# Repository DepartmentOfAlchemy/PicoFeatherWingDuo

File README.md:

# ProtoPropDuo
Breakout board allowing a Raspberry Pi Pico to interface with up to two FeatherWing boards.

RP2040 Peripheral Usage for Feather Wings

SPI:
  * SCK: SPI1 SCK
  * MOSI: SPI1 TX
  * MISO: SPI1 RX

I2C:
  * SDA: I2C1 SDA
  * SCL: I2C1 SCL

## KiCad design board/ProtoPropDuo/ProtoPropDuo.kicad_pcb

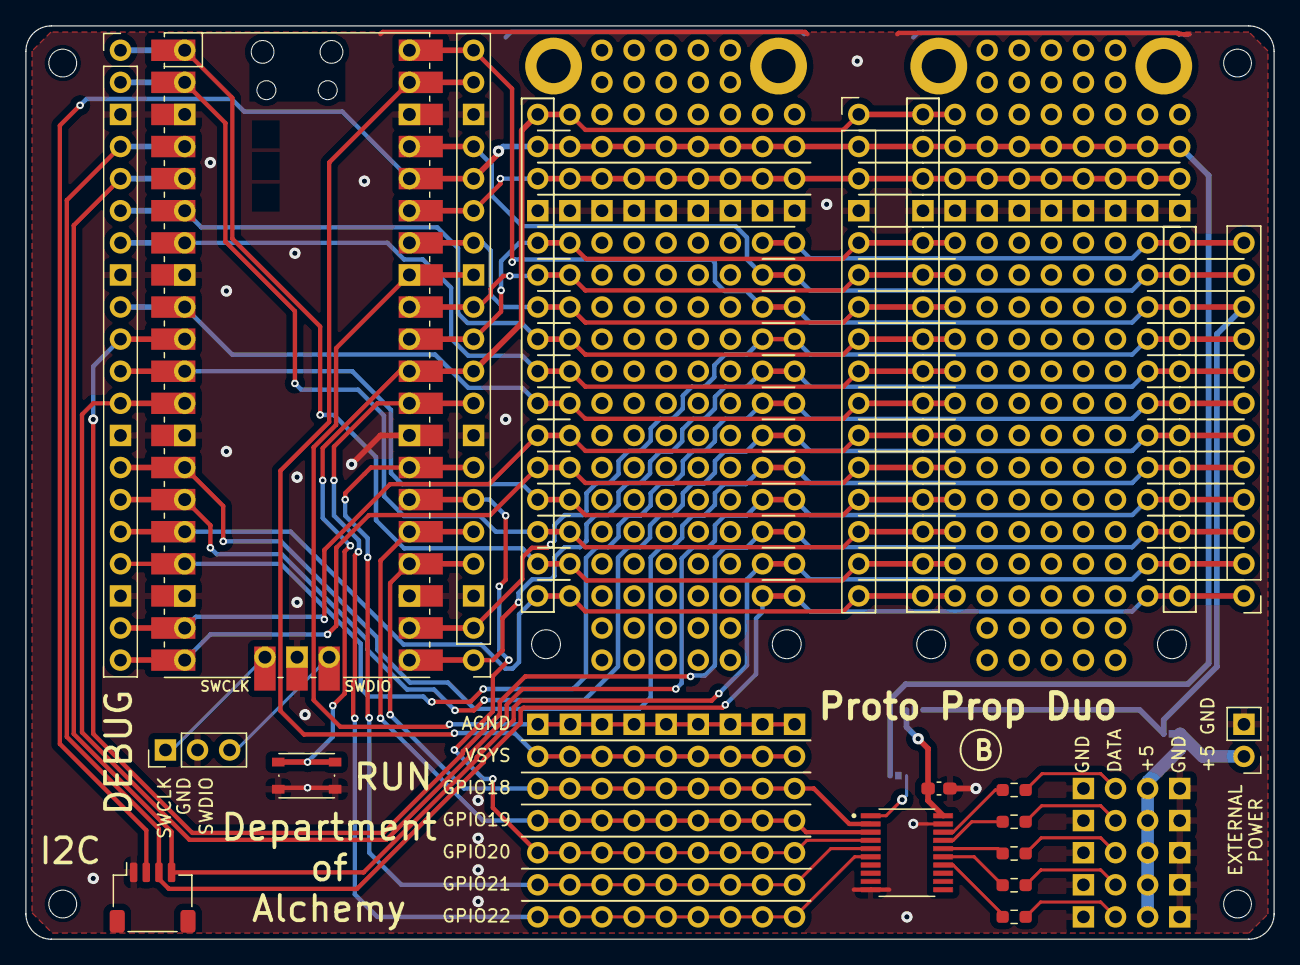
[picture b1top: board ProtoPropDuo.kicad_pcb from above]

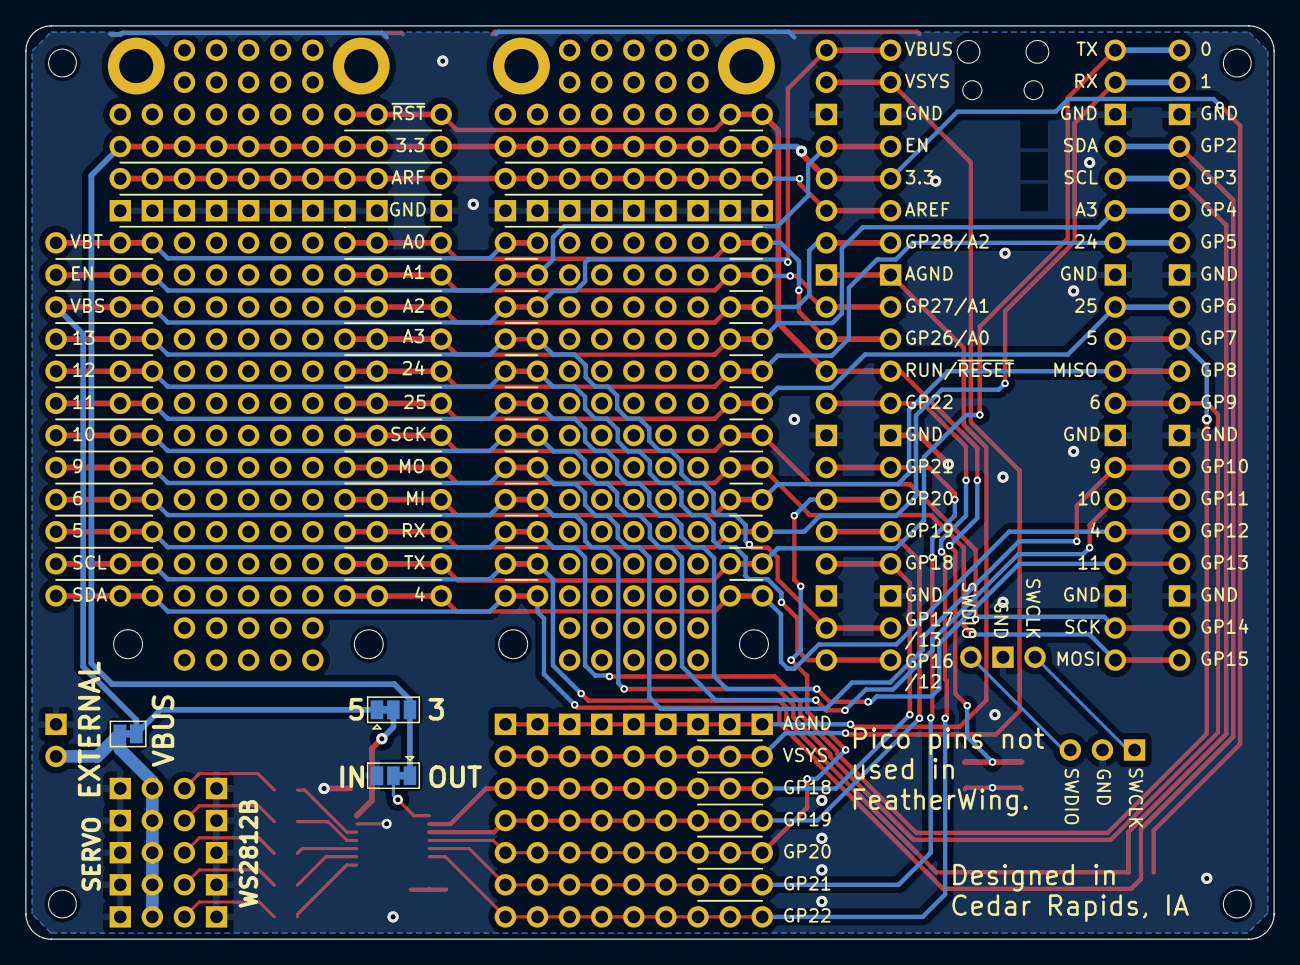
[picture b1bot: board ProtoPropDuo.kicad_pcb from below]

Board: 2 copper layers, 98.8 x 72.3 mm, 183 parts (3 on the bottom side), 50 nets.

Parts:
A1, A2: Adafruit_Feather_Generic; Feather Pins
C1: 0.1uF; C_0603_1608Metric_Pad1.08x0.95mm_HandSolder
H1, H2, H3, H4: MountingHole; MountingHole_2.2mm_M2_ISO14580
J1: Conn_01x04; JST_SH_SM04B-SRSS-TB_1x04-1MP_P1.00mm_Horizontal
J2: Conn_01x07; PinHeader_1x07_P2.54mm_Vertical
J3, J4: Conn_01x20; PinHeader_1x20_P2.54mm_Vertical
J5: Conn_01x16; PinHeader_1x16_P2.54mm_Vertical
J6: Conn_01x12; PinHeader_1x12_P2.54mm_Vertical
J7, J8, J9, J10, J11, J12, J13, J14, J15, J16, J17, J18, J19, J20, J21, J22, J23, J24, J25, J26, J27, J28, J29, J30, J31, J32, J33, J34, J35, J36, J37, J38, J39, J40, J41, J42, J43, J44, J45, J46, J47, J48, J49, J50, J51, J52, J53, J54, J55, J56, J57, J58, J59, J60, J61, J62, J63, J64, J65, J66, J67, J68, J69, J70, J71, J72, J73, J74, J75, J76, J77, J78, J79, J80, J81, J82, J83, J84, J85, J86, J87, J88, J89, J90, J91, J92, J93, J94, J95, J96, J97, J98, J99, J100, J101, J102, J103, J104, J105, J107, J108, J109, J110, J110#2, J110#3, J110#4, J110#5, J110#6, J110#7, J111, J113, J113#2, J113#3, J113#4, J113#5, J113#6, J114, J114#2, J114#3, J114#4, J114#5, J114#6, J114#7, J115, J115#2, J115#3, J115#4, J115#5, J115#6, J115#7, J116, J116#2, J116#3, J116#4, J116#5, J116#6, J116#7, J117, J118, J118#2, J118#3, J118#4, J118#5, J118#6, J118#7, J119, J120, J120#2, J120#3, J120#4, J120#5, J120#6, J120#7: Conn_01x01; Grid Hole
J106, J112, J124: Conn_01x05; PinHeader_1x05_P2.54mm_Vertical
J121: Conn_01x03; PinHeader_1x03_P2.54mm_Vertical
J122: Conn_01x02; PinHeader_1x02_P2.54mm_Vertical
J123: Conn_01x05_Extra_Output; PinHeader_1x05_P2.54mm_Vertical
JP1: SolderJumper_2_Bridged; SolderJumper-2_P1.3mm_Bridged_Pad1.0x1.5mm
JP2, JP3: SolderJumper_3_Bridged12; SolderJumper-3_P1.3mm_Bridged12_Pad1.0x1.5mm
R1, R2, R3, R4, R5: 300; R_0603_1608Metric_Pad0.98x0.95mm_HandSolder
SW2: SW_Push; SW_Push_1P1T_NO_RKB2SJK250SMTR LFS
U1: Pico; RPi_Pico_SMD_TH
U2: SOP65P640X120-20N

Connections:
+3.3V: A1.2 (3V3), A2.2 (3V3), J1.2, J4.16, J5.2, J9.1, J37.1, J92.1, J93.1, J94.1, J95.1, J96.1, J97.1, J98.1, J99.1, J100.1, J101.1, J102.1, J103.1, J104.1, J105.1, JP2.3 (B), JP3.1 (A), U1.36 (3V3)
+5V: J106.1, J106.2, J106.3, J106.4, J106.5, J122.1, JP1.2 (B)
/A0: A1.5 (A0), A2.5 (A0), J4.11, J5.5, J12.1, J40.1, U1.31 (GPIO26_ADC0)
/A1: A1.6 (A1), A2.6 (A1), J4.12, J5.6, J13.1, J41.1, U1.32 (GPIO27_ADC1)
/A2: A1.7 (A2), A2.7 (A2), J4.14, J5.7, J14.1, J42.1, U1.34 (GPIO28_ADC2)
/A3: A1.8 (A3), A2.8 (A3), J3.6, J5.8, J15.1, J43.1, U1.6 (GPIO4)
/AGND: J2.1, J4.13, J119.1, J120.1, J120#2.1, J120#3.1, J120#4.1, J120#5.1, J120#6.1, J120#7.1, U1.33 (AGND)
/AREF: A1.3 (AREF), A2.3 (AREF), J4.15, J5.3, J10.1, J38.1, J78.1, J79.1, J80.1, J81.1, J82.1, J83.1, J84.1, J85.1, J86.1, J87.1, J88.1, J89.1, J90.1, J91.1, U1.35 (ADC_VREF)
/D4: A1.16 (SPARE), A2.16 (SPARE), J3.16, J5.16, J23.1, J51.1, U1.16 (GPIO12)
/D5: A1.19 (D5), A2.19 (D5), J3.10, J6.3, J33.1, J61.1, U1.10 (GPIO7)
/D6: A1.20 (D6), A2.20 (D6), J3.12, J6.4, J32.1, J60.1, U1.12 (GPIO9)
/D9: A1.21 (D9), A2.21 (D9), J3.14, J6.5, J31.1, J59.1, U1.14 (GPIO10)
/D10: A1.22 (D10), A2.22 (D10), J3.15, J6.6, J30.1, J58.1, U1.15 (GPIO11)
/D11: A1.23 (D11), A2.23 (D11), J3.17, J6.7, J29.1, J57.1, U1.17 (GPIO13)
/D12: A1.24 (D12), A2.24 (D12), J4.1, J6.8, J28.1, J56.1, U1.21 (GPIO16)
/D13: A1.25 (D13), A2.25 (D13), J4.2, J6.9, J27.1, J55.1, U1.22 (GPIO17)
/D24: A1.9 (A4), A2.9 (A4), J3.7, J5.9, J16.1, J44.1, U1.7 (GPIO5)
/D25: A1.10 (A5), A2.10 (A5), J3.9, J5.10, J17.1, J45.1, U1.9 (GPIO6)
/EN: A1.27 (EN), A2.27 (EN), J4.17, J6.11, J25.1, J53.1, U1.37 (3V3_EN)
/GPIO18: J2.3, J4.4, J110.1, J110#2.1, J110#3.1, J110#4.1, J110#5.1, J110#6.1, J110#7.1, J117.1, U1.24 (GPIO18), U2.2 (A0)
/GPIO19: J2.4, J4.5, J109.1, J116.1, J116#2.1, J116#3.1, J116#4.1, J116#5.1, J116#6.1, J116#7.1, U1.25 (GPIO19), U2.3 (A1)
/GPIO20: J2.5, J4.6, J108.1, J115.1, J115#2.1, J115#3.1, J115#4.1, J115#5.1, J115#6.1, J115#7.1, U1.26 (GPIO20), U2.4 (A2)
/GPIO21: J2.6, J4.7, J107.1, J114.1, J114#2.1, J114#3.1, J114#4.1, J114#5.1, J114#6.1, J114#7.1, U1.27 (GPIO21), U2.5 (A3)
/GPIO22: J2.7, J4.9, J7.1, J113.1, J113#2.1, J113#3.1, J113#4.1, J113#5.1, J113#6.1, U1.29 (GPIO22), U2.6 (A4)
/MISO: A1.13 (MISO), A2.13 (MISO), J3.11, J5.13, J20.1, J48.1, U1.11 (GPIO8)
/MOSI: A1.12 (MOSI), A2.12 (MOSI), J3.20, J5.12, J19.1, J47.1, U1.20 (GPIO15)
/RX: A1.14 (RX), A2.14 (RX), J3.2, J5.14, J21.1, J49.1, U1.2 (GPIO1)
/SCK: A1.11 (SCK), A2.11 (SCK), J3.19, J5.11, J18.1, J46.1, U1.19 (GPIO14)
/SCL: A1.18 (SCL), A2.18 (SCL), J1.4, J3.5, J6.2, J34.1, J62.1, U1.5 (GPIO3)
/SDA: A1.17 (SDA), A2.17 (SDA), J1.3, J3.4, J6.1, J35.1, J63.1, U1.4 (GPIO2)
/SWCLK: J121.1, U1.41 (SWCLK)
/SWDIO: J121.3, U1.43 (SWDIO)
/TX: A1.15 (TX), A2.15 (TX), J3.1, J5.15, J22.1, J50.1, U1.1 (GPIO0)
/VBAT: A1.28 (VBAT), A2.28 (VBAT), J6.12, J24.1, J52.1
/VBUS: A1.26 (USB), A2.26 (USB), J4.20, J6.10, J26.1, J54.1, JP1.1 (A), JP2.1 (A), U1.40 (VBUS)
/VSYS: J2.2, J4.19, J111.1, J118.1, J118#2.1, J118#3.1, J118#4.1, J118#5.1, J118#6.1, J118#7.1, U1.39 (VSYS)
/~RESET: A1.1 (~RESET), A2.1 (~RESET), J4.10, J5.1, J8.1, J36.1, SW2.1, U1.30 (RUN)
GND: A1.4 (GND), A2.4 (GND), C1.2, J1.1, J3.3, J3.8, J3.13, J3.18, J4.3, J4.8, J4.18, J5.4, J11.1, J39.1, J64.1, J65.1, J66.1, J67.1, J68.1, J69.1, J70.1, J71.1, J72.1, J73.1, J74.1, J75.1, J76.1, J77.1, J112.1, J112.2, J112.3, J112.4, J112.5, J121.2, J122.2, J124.1, J124.2, J124.3, J124.4, J124.5, JP3.3 (B), SW2.2, U1.3 (GND), U1.8 (GND), U1.13 (GND), U1.18 (GND), U1.23 (GND), U1.28 (GND), U1.38 (GND), U1.42 (GND), U2.10 (GND), U2.19 (OE)
unnamed: J123.1, R1.2
unnamed: J123.2, R2.2
unnamed: J123.3, R3.2
unnamed: J123.4, R4.2
unnamed: J123.5, R5.2
unnamed: C1.1, JP2.2 (C), U2.20 (VCC)
unnamed: JP3.2 (C), U2.1 (DIR)
unnamed: R1.1, U2.18 (B0)
unnamed: R2.1, U2.17 (B1)
unnamed: R3.1, U2.16 (B2)
unnamed: R4.1, U2.15 (B3)
unnamed: R5.1, U2.14 (B4)

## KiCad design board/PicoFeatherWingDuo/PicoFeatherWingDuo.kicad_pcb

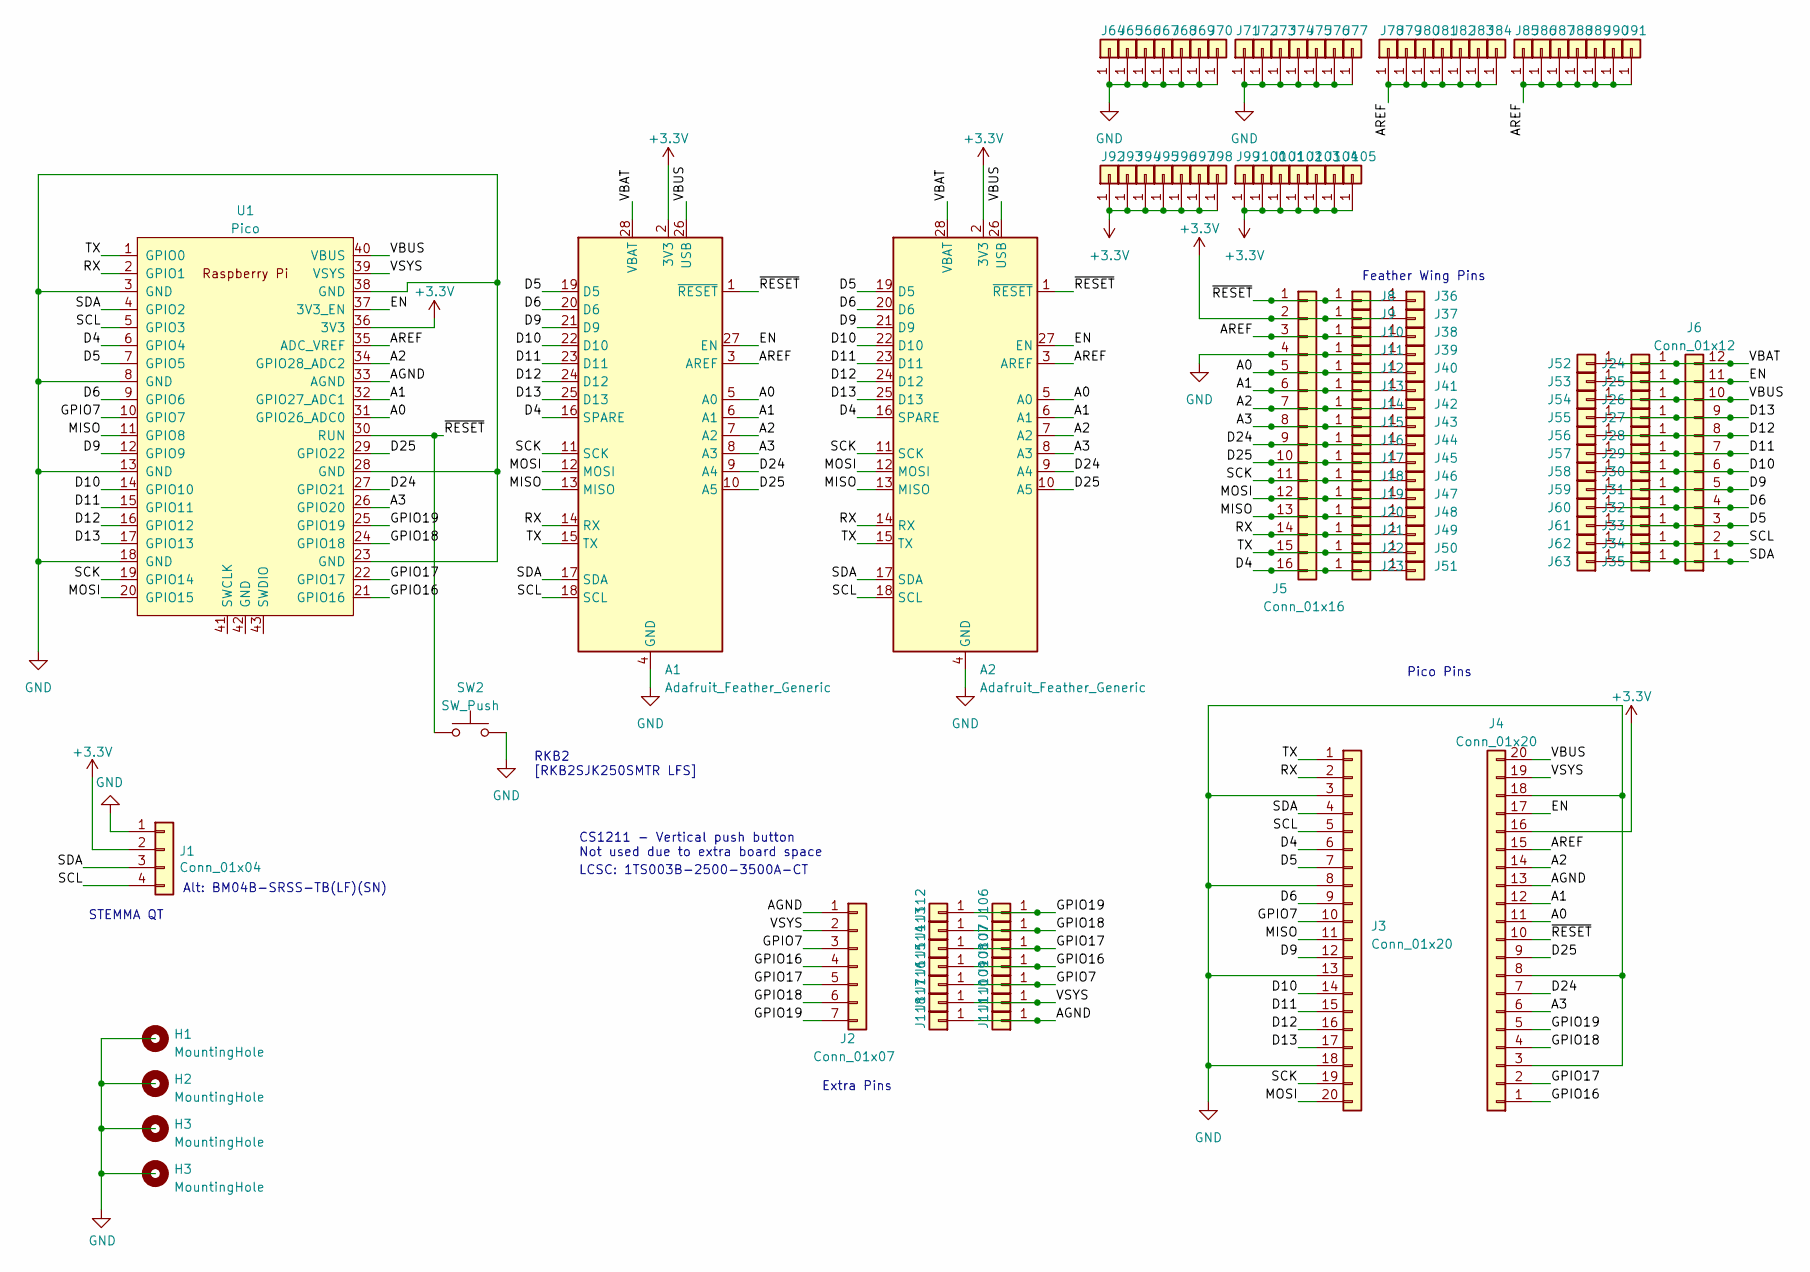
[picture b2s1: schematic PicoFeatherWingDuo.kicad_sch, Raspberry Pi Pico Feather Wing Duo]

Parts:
A1, A2: Adafruit_Feather_Generic; Feather Pins
H1, H2, H3: MountingHole; MountingHole_2.2mm_M2_ISO14580
J1: Conn_01x04; JST_SH_SM04B-SRSS-TB_1x04-1MP_P1.00mm_Horizontal
J2: Conn_01x07; PinHeader_1x07_P2.54mm_Vertical
J3, J4: Conn_01x20; PinHeader_1x20_P2.54mm_Vertical
J5: Conn_01x16; PinHeader_1x16_P2.54mm_Vertical
J6: Conn_01x12; PinHeader_1x12_P2.54mm_Vertical
J7, J8, J9, J10, J11, J12, J13, J14, J15, J16, J17, J18, J19, J20, J21, J22, J23, J24, J25, J26, J27, J28, J29, J30, J31, J32, J33, J34, J35, J36, J37, J38, J39, J40, J41, J42, J43, J44, J45, J46, J47, J48, J49, J50, J51, J52, J53, J54, J55, J56, J57, J58, J59, J60, J61, J62, J63, J64, J65, J66, J67, J68, J69, J70, J71, J72, J73, J74, J75, J76, J77, J78, J79, J80, J81, J82, J83, J84, J85, J86, J87, J88, J89, J90, J91, J92, J93, J94, J95, J96, J97, J98, J99, J100, J101, J102, J103, J104, J105, J106, J107, J108, J109, J110, J111, J112, J113, J114, J115, J116, J117, J118: Conn_01x01; Grid Hole
SW2: SW_Push; SW_Push_1P1T_NO_RKB2SJK250SMTR LFS
U1: Pico; RPi_Pico_SMD_TH

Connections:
+3.3V: A1.2 (3V3), A2.2 (3V3), J1.2, J4.16, J5.2, J9.1, J37.1, J92.1, J93.1, J94.1, J95.1, J96.1, J97.1, J98.1, J99.1, J100.1, J101.1, J102.1, J103.1, J104.1, J105.1, U1.36 (3V3)
/A0: A1.5 (A0), A2.5 (A0), J4.11, J5.5, J12.1, J40.1, U1.31 (GPIO26_ADC0)
/A1: A1.6 (A1), A2.6 (A1), J4.12, J5.6, J13.1, J41.1, U1.32 (GPIO27_ADC1)
/A2: A1.7 (A2), A2.7 (A2), J4.14, J5.7, J14.1, J42.1, U1.34 (GPIO28_ADC2)
/A3: A1.8 (A3), A2.8 (A3), J4.6, J5.8, J15.1, J43.1, U1.26 (GPIO20)
/AGND: J2.1, J4.13, J111.1, J118.1, U1.33 (AGND)
/AREF: A1.3 (AREF), A2.3 (AREF), J4.15, J5.3, J10.1, J38.1, J78.1, J79.1, J80.1, J81.1, J82.1, J83.1, J84.1, J85.1, J86.1, J87.1, J88.1, J89.1, J90.1, J91.1, U1.35 (ADC_VREF)
/D4: A1.16 (SPARE), A2.16 (SPARE), J3.6, J5.16, J23.1, J51.1, U1.6 (GPIO4)
/D5: A1.19 (D5), A2.19 (D5), J3.7, J6.3, J33.1, J61.1, U1.7 (GPIO5)
/D6: A1.20 (D6), A2.20 (D6), J3.9, J6.4, J32.1, J60.1, U1.9 (GPIO6)
/D9: A1.21 (D9), A2.21 (D9), J3.12, J6.5, J31.1, J59.1, U1.12 (GPIO9)
/D10: A1.22 (D10), A2.22 (D10), J3.14, J6.6, J30.1, J58.1, U1.14 (GPIO10)
/D11: A1.23 (D11), A2.23 (D11), J3.15, J6.7, J29.1, J57.1, U1.15 (GPIO11)
/D12: A1.24 (D12), A2.24 (D12), J3.16, J6.8, J28.1, J56.1, U1.16 (GPIO12)
/D13: A1.25 (D13), A2.25 (D13), J3.17, J6.9, J27.1, J55.1, U1.17 (GPIO13)
/D24: A1.9 (A4), A2.9 (A4), J4.7, J5.9, J16.1, J44.1, U1.27 (GPIO21)
/D25: A1.10 (A5), A2.10 (A5), J4.9, J5.10, J17.1, J45.1, U1.29 (GPIO22)
/EN: A1.27 (EN), A2.27 (EN), J4.17, J6.11, J25.1, J53.1, U1.37 (3V3_EN)
/GPIO7: J2.3, J3.10, J109.1, J116.1, U1.10 (GPIO7)
/GPIO16: J2.4, J4.1, J108.1, J115.1, U1.21 (GPIO16)
/GPIO17: J2.5, J4.2, J107.1, J114.1, U1.22 (GPIO17)
/GPIO18: J2.6, J4.4, J7.1, J113.1, U1.24 (GPIO18)
/GPIO19: J2.7, J4.5, J106.1, J112.1, U1.25 (GPIO19)
/MISO: A1.13 (MISO), A2.13 (MISO), J3.11, J5.13, J20.1, J48.1, U1.11 (GPIO8)
/MOSI: A1.12 (MOSI), A2.12 (MOSI), J3.20, J5.12, J19.1, J47.1, U1.20 (GPIO15)
/RX: A1.14 (RX), A2.14 (RX), J3.2, J5.14, J21.1, J49.1, U1.2 (GPIO1)
/SCK: A1.11 (SCK), A2.11 (SCK), J3.19, J5.11, J18.1, J46.1, U1.19 (GPIO14)
/SCL: A1.18 (SCL), A2.18 (SCL), J1.4, J3.5, J6.2, J34.1, J62.1, U1.5 (GPIO3)
/SDA: A1.17 (SDA), A2.17 (SDA), J1.3, J3.4, J6.1, J35.1, J63.1, U1.4 (GPIO2)
/TX: A1.15 (TX), A2.15 (TX), J3.1, J5.15, J22.1, J50.1, U1.1 (GPIO0)
/VBAT: A1.28 (VBAT), A2.28 (VBAT), J6.12, J24.1, J52.1
/VBUS: A1.26 (USB), A2.26 (USB), J4.20, J6.10, J26.1, J54.1, U1.40 (VBUS)
/VSYS: J2.2, J4.19, J110.1, J117.1, U1.39 (VSYS)
/~RESET: A1.1 (~RESET), A2.1 (~RESET), J4.10, J5.1, J8.1, J36.1, SW2.1, U1.30 (RUN)
GND: A1.4 (GND), A2.4 (GND), J1.1, J3.3, J3.8, J3.13, J3.18, J4.3, J4.8, J4.18, J5.4, J11.1, J39.1, J64.1, J65.1, J66.1, J67.1, J68.1, J69.1, J70.1, J71.1, J72.1, J73.1, J74.1, J75.1, J76.1, J77.1, SW2.2, U1.3 (GND), U1.8 (GND), U1.13 (GND), U1.18 (GND), U1.23 (GND), U1.28 (GND), U1.38 (GND)

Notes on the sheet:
Extra Pins
RKB2 [RKB2SJK250SMTR LFS]
Pico Pins
LCSC: 1TS003B-2500-3500A-CT
Alt: BM04B-SRSS-TB(LF)(SN)
STEMMA QT
CS1211 - Vertical push button Not used due to extra board space
Feather Wing Pins

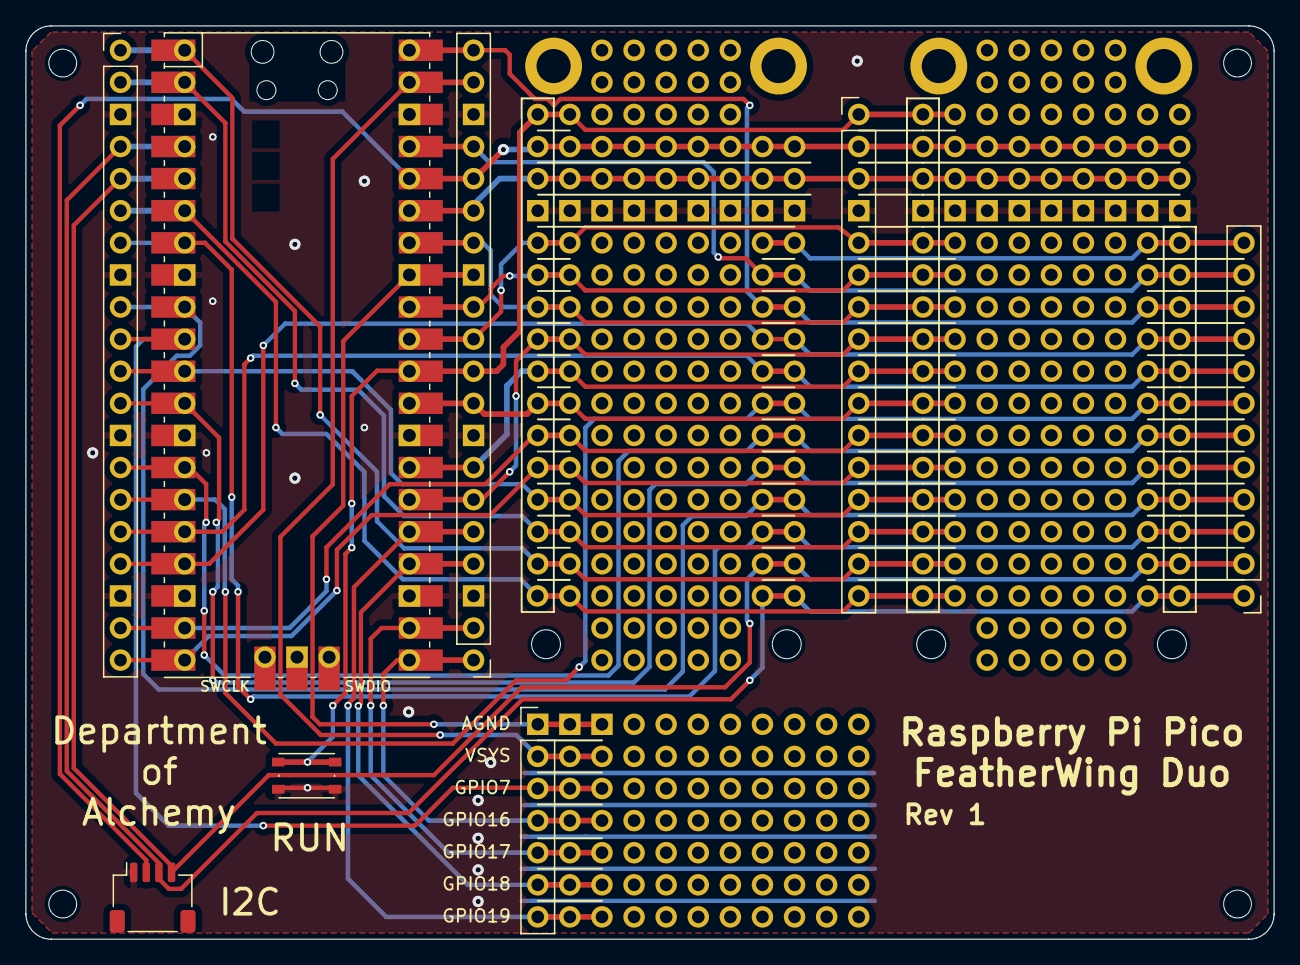
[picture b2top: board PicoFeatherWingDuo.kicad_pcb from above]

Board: 2 copper layers, 98.8 x 72.3 mm, 126 parts (0 on the bottom side), 35 nets.

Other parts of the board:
H4: MountingHole; MountingHole_2.2mm_M2_ISO14580

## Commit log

2023-06-13 Revision 1. Initial commit with Rev 1 of the board. Have ordered a Rev 1 board to be created for prototype testing.
2023-09-08 Rev B: Reworked the mapping from Pico to featherwing to align some pins for PIO and pwm channels. Added level shifter to support ws2812b individually addressable RGB lights and support for and extern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
2023-09-08 Update README.md
    Updated to represent the new project name.
2023-09-08 Rev B gerbers sent for fabrication 20230908.
2023-11-01 Added support for ambient and triggered audio.
2023-11-02 Added support for ambient and triggered output configuration via the 'config.toml' configuration file.
2023-11-02 Added support for a default scene if the SD card isn't provided.
2023-12-16 Update README.md
    Added documentation about the RP2040 peripherals used for the Feather Wing interface.
